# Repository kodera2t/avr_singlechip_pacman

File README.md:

# avr_singlechip_pacman
In fact, I just made a circuit board, and wrote .hex file relased by a great programmer. hex file can be downloaded from 
https://f4533dfbeaefeec681df4fa05f4af1fa6b86af7d.googledrive.com/host/0B0iYjz8Pd5FjMjBBNWFMRktrWEE/index.htm
( from the top link of the website..) Actually this is a great surprise for me to complete perfect pacman just one chip!!

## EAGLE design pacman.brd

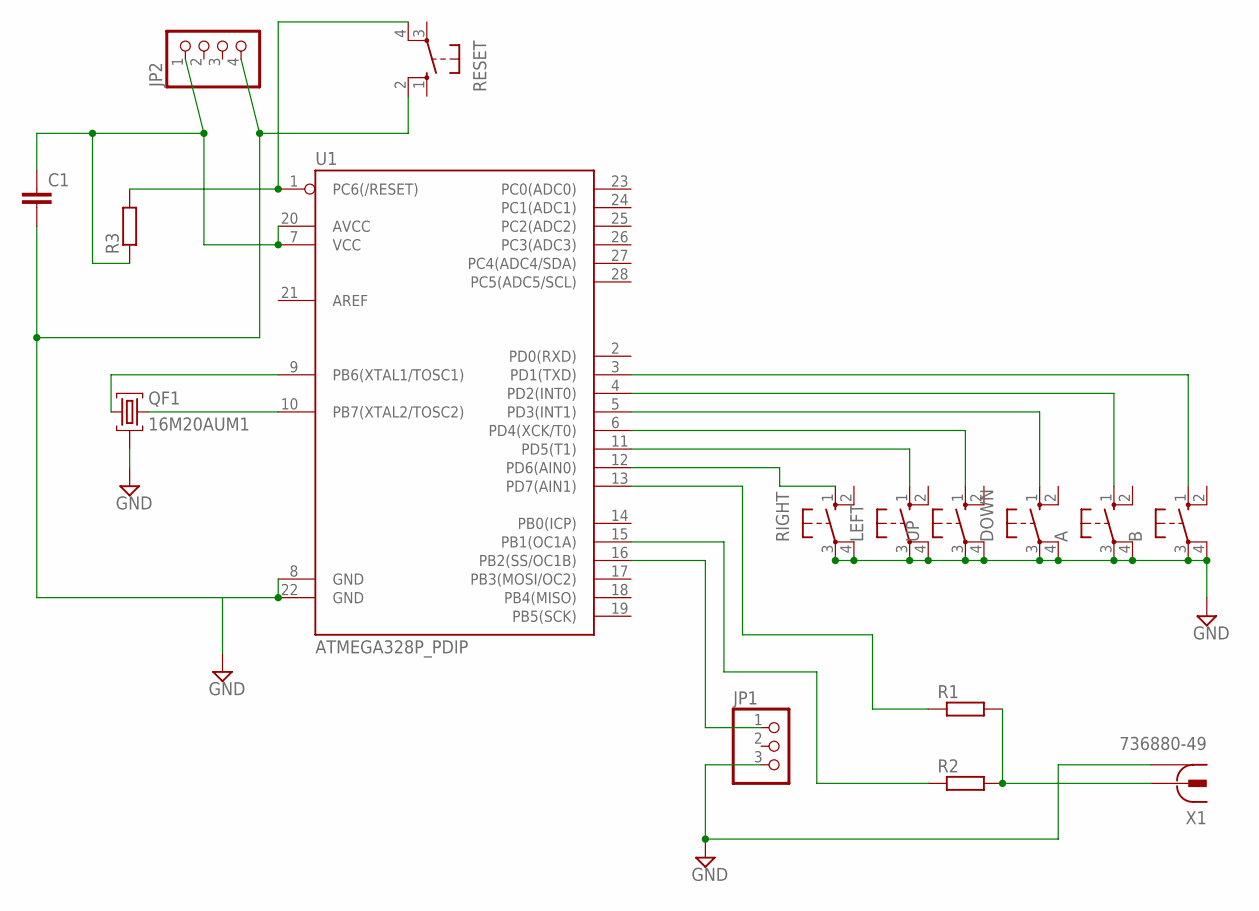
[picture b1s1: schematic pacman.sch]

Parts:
A: 10-XX; B3F-10XX
B: 10-XX; B3F-10XX
C1: CC3225; C3225
DOWN: 10-XX; B3F-10XX
JP1: PINHD-1X3; 1X03
JP2: PINHD-1X4; 1X04
LEFT: 10-XX; B3F-10XX
QF1: 16M20AUM1; UM1
R1, R2, R3: RR0603; R0603
RESET: 10-XX; B3F-10XX
RIGHT: 10-XX; B3F-10XX
U1: ATMEGA328P_PDIP; DIL28-3
UP: 10-XX; B3F-10XX
X1: 736880-49

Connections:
GND: A.3, A.4 (P1), B.3, B.4 (P1), C1.2, DOWN.3, DOWN.4 (P1), JP1.3, JP2.4, LEFT.3, LEFT.4 (P1), QF1.2, RESET.2 (S1), RIGHT.3, RIGHT.4 (P1), U1.8 (GND), U1.22 (GND), UP.3, UP.4 (P1), X1.1, X1.1@1 (1), X1.1@2 (1)
unnamed: RIGHT.1 (S), U1.12 (PD6(AIN0))
unnamed: LEFT.1 (S), U1.11 (PD5(T1))
unnamed: U1.6 (PD4(XCK/T0)), UP.1 (S)
unnamed: DOWN.1 (S), U1.5 (PD3(INT1))
unnamed: A.1 (S), U1.4 (PD2(INT0))
unnamed: B.1 (S), U1.3 (PD1(TXD))
unnamed: JP1.1, U1.16 (PB2(SS/OC1B))
unnamed: R2.1, U1.15 (PB1(OC1A))
unnamed: R1.1, U1.13 (PD7(AIN1))
unnamed: R1.2, R2.2, X1.2
unnamed: C1.1, JP2.1, R3.1, U1.7 (VCC), U1.20 (AVCC)
unnamed: QF1.3, U1.10 (PB7(XTAL2/TOSC2))
unnamed: QF1.1, U1.9 (PB6(XTAL1/TOSC1))
unnamed: R3.2, RESET.4 (P1), U1.1 (PC6(/RESET))

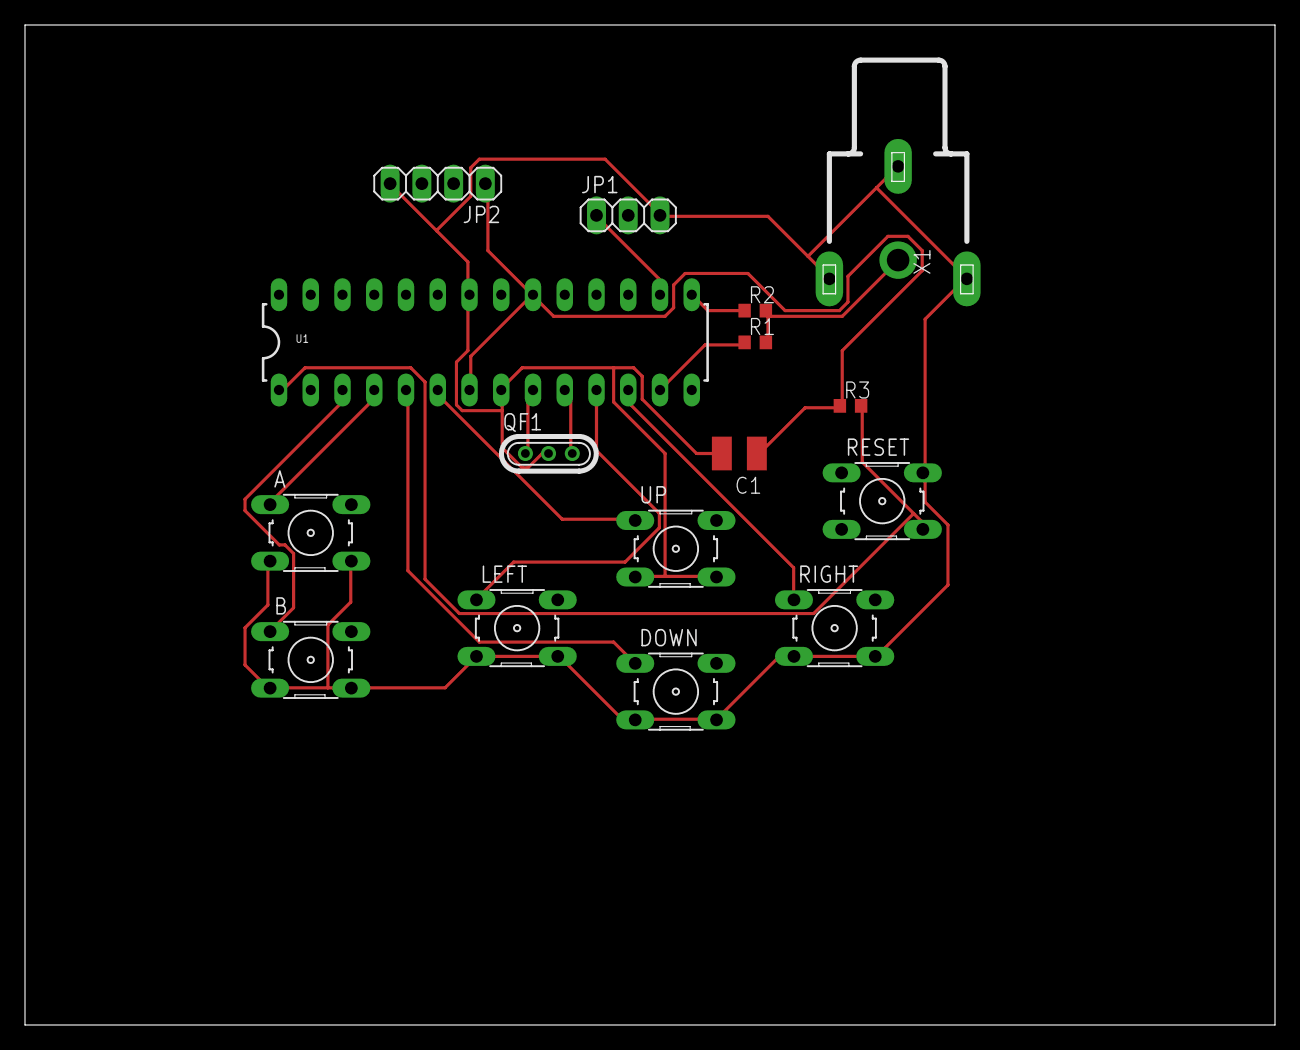
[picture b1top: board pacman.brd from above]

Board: 2 copper layers, 100.0 x 80.0 mm, 16 parts (0 on the bottom side), 15 nets.

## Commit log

2015-02-21 initial submission
2015-02-24 gerber datas

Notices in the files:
parts and their libraries:
SparkFun-DigitalIC: Licensing: Creative Commons ShareAlike 4.0 International - https://creativecommons.org/licenses/by-sa/4.0
